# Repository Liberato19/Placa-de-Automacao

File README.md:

# Controle de Disjuntores com ESP32, Tasmota e Home Assistant

## Descrição do Projeto
Este projeto apresenta o desenvolvimento de uma placa de automação projetada para controlar **disjuntores** através de um **ESP32** com o firmware **Tasmota** instalado. O ESP32 atua como endpoint MQTT, e todas as informações e controles são exibidos no **Home Assistant**.

## Visão Geral do Projeto

### Imagem da Placa

A placa foi projetada para facilitar o controle remoto dos disjuntores, garantindo um sistema robusto e integrado.

---

## Instalação do Firmware Tasmota no ESP32

Para utilizar a placa, é necessário instalar o firmware **Tasmota** no ESP32. Certifique-se de configurar corretamente o MQTT com o seu próprio broker e seguir a pinagem descrita abaixo:

### Interface Inicial do Tasmota

### Configuração de Pinagem no Tasmota

---

## Configuração do Home Assistant

### 1. Configurar o Broker MQTT
No **Home Assistant**, configure seu Broker MQTT para a comunicação com o dispositivo Tasmota.

Assim que o MQTT estiver configurado corretamente, o dispositivo deve ser detectado automaticamente.

### Integração com o MQTT no Home Assistant

### Integração com o Tasmota

---

## Configuração da Dashboard no Home Assistant

Com a integração concluída, os botões de controle dos disjuntores podem ser adicionados à **dashboard** do Home Assistant. Isso permite o controle direto dos disjuntores com apenas um clique.

### Planta Integrada

### Botões de Controle

---

## Requisitos
- **ESP32**
- **Placa de automação**
- **Firmware Tasmota**
- **Broker MQTT** (local ou em nuvem)
- **Home Assistant** configurado

---

## Tags de Tecnologias Utilizadas

---

## Guia de Uso
1. Instale o firmware **Tasmota** no ESP32 e configure o MQTT.
2. Conecte o ESP32 à placa de automação.
3. Configure o Broker MQTT no Home Assistant.
4. Integre o dispositivo Tasmota no Home Assistant.
5. Adicione os botões à dashboard e comece a controlar os disjuntores!

---

## Imagens do Projeto

1. **PCB da Placa** 
2. **Interface Inicial do Tasmota** 
3. **Configuração de Pinagem** 
4. **Integração MQTT no Home Assistant** 
5. **Integração com o Tasmota** 

---

## Licença
Este projeto está licenciado sob a **MIT License**.

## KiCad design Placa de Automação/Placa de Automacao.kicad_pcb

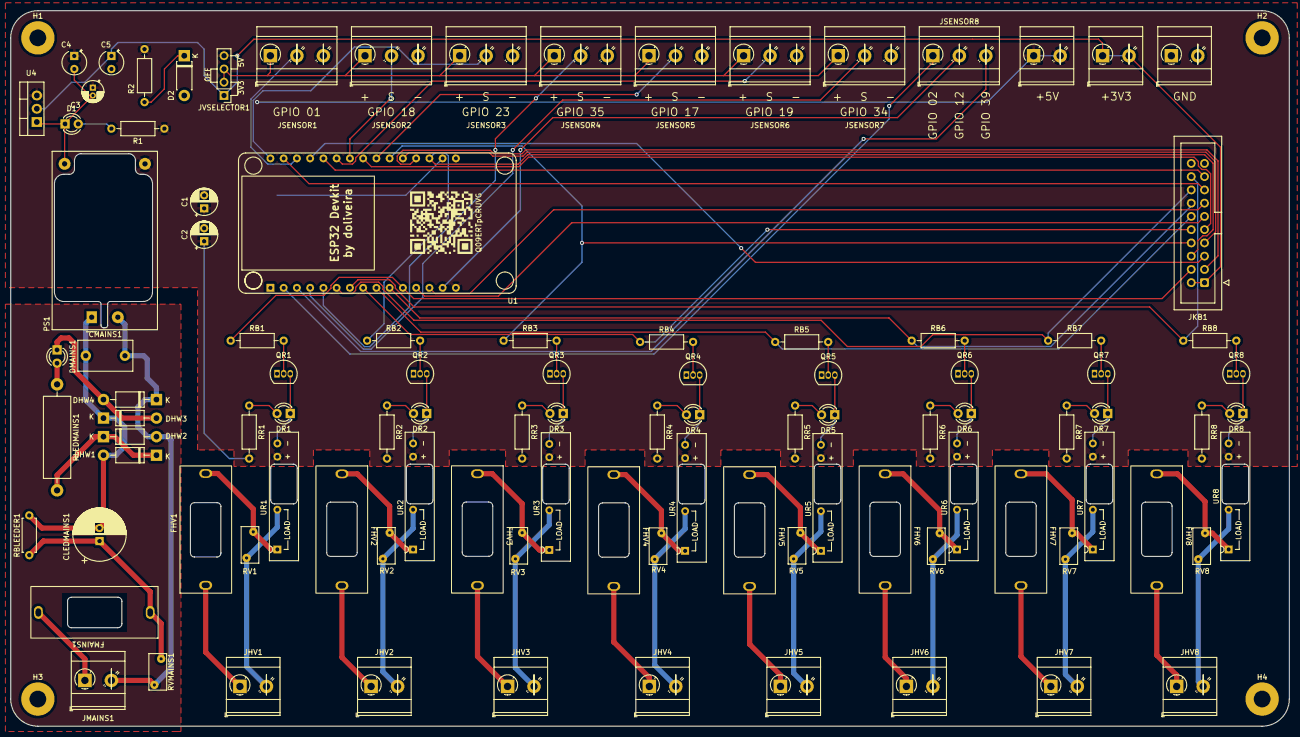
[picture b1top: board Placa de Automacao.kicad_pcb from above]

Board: 2 copper layers, 245.1 x 137.1 mm, 106 parts (0 on the bottom side), 87 nets.

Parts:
C1, C2: 10 uF; CP_Radial_D5.0mm_P2.50mm
C3: 220 uF; CP_Radial_D4.0mm_P1.50mm
C4, C5: 10 uF; CP_Radial_Tantal_D4.5mm_P2.50mm
CLEDMAINS1: 33uF; CP_Radial_D10.0mm_P2.50mm
CMAINS1: 0.1uF; C_Rect_L10.3mm_W5.7mm_P7.50mm_MKS4
D1: LED; LED_D3.0mm
D2: 5V1; D_DO-41_SOD81_P7.62mm_Horizontal
DHW1, DHW2, DHW3, DHW4: 1N4007; D_DO-41_SOD81_P10.16mm_Horizontal
DMAINS1: LED; LED_D3.0mm
DR1, DR2, DR3, DR4, DR5, DR6, DR7, DR8: LED; LED_D3.0mm
FHV1, FHV2, FHV3, FHV4, FHV5, FHV6, FHV7, FHV8: 1A; Fuseholder_Cylinder-5x20mm_Generic_Horizontal_Closed
FMAINS1: 0.5A; Fuseholder_Cylinder-5x20mm_Generic_Horizontal_Closed
G6: LOGO
H1, H2, H3, H4: MountingHole; MountingHole_3.2mm_M3_Pad
JHV1, JHV2, JHV3, JHV4, JHV5, JHV6, JHV7, JHV8: Screw_Terminal_01x02; TerminalBlock_MetzConnect_Type073_RT02602HBLU_1x02_P5.08mm_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
JKB1: Conn_02x10_Top_Bottom; IDC-Header_2x10_P2.54mm_Vertical
JMAINS1: Screw_Terminal_01x02; TerminalBlock_MetzConnect_Type073_RT02602HBLU_1x02_P5.08mm_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
JSENSOR1, JSENSOR2, JSENSOR3, JSENSOR4, JSENSOR5, JSENSOR6, JSENSOR7, JSENSOR8: Screw_Terminal_01x03; TerminalBlock_MetzConnect_Type073_RT02603HBLU_1x03_P5.08mm_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
JVSELECTOR1: Conn_01x04_Pin; PinHeader_1x04_P2.54mm_Vertical
J_GND1: Screw_Terminal_01x02; TerminalBlock_MetzConnect_Type073_RT02602HBLU_1x02_P5.08mm_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
J_POS_3V1, J_POS_5V1: Screw_Terminal_01x02; TerminalBlock_MetzConnect_Type073_RT02602HBLU_1x02_P5.08mm_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
PS1: HLK-PM01; Converter_ACDC_HiLink_HLK-PMxx
QR1, QR2, QR3, QR4, QR5, QR6, QR7, QR8: PN2222A; TO-92_Inline
R1: 160; R_Axial_DIN0207_L6.3mm_D2.5mm_P10.16mm_Horizontal
R2: 10; R_Axial_DIN0207_L6.3mm_D2.5mm_P10.16mm_Horizontal
RB1, RB2, RB3, RB4, RB5, RB6, RB7, RB8: 56; R_Axial_DIN0207_L6.3mm_D2.5mm_P10.16mm_Horizontal
RBLEEDER1: 1M; R_Axial_DIN0207_L6.3mm_D2.5mm_P7.62mm_Horizontal
RLEDMAINS1: 56k; R_Axial_DIN0516_L15.5mm_D5.0mm_P20.32mm_Horizontal
RR1, RR2, RR3, RR4, RR5, RR6, RR7, RR8: 150; R_Axial_DIN0207_L6.3mm_D2.5mm_P10.16mm_Horizontal
RV1, RV2, RV3, RV4, RV5, RV6, RV7, RV8: 250 VAC; RV_Disc_D7mm_W3.4mm_P5mm
RVMAINS1: 250 VAC; RV_Disc_D7mm_W3.4mm_P5mm
U1: ESP32_Devkit_Generic_Alt; ESP32_Devkit
U4: LM1117-3.3; TO-220-3_Vertical
UR1, UR2, UR3, UR4, UR5, UR6, UR7, UR8: G3MB-202P; PTH_W24.5_D5.5_SSR_OMRON_G3MB-202P

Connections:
+3V3: C5.1, JKB1.1, JKB1.2, JVSELECTOR1.1, J_POS_3V1.1, J_POS_3V1.2, U4.2 (VO)
+5V: C1.1, C2.1, C3.1, C4.1, JVSELECTOR1.4, J_POS_5V1.1, J_POS_5V1.2, PS1.4 (+Vout), R1.1, R2.1, RR1.2, RR2.2, RR3.2, RR4.2, RR5.2, RR6.2, RR7.2, RR8.2, U1.15 (VIN), U4.3 (VI), UR1.3, UR2.3, UR3.3, UR4.3, UR5.3, UR6.3, UR7.3, UR8.3
/volt_selector: JSENSOR1.1, JSENSOR2.1, JSENSOR3.1, JSENSOR4.1, JSENSOR5.1, JSENSOR6.1, JSENSOR7.1, JVSELECTOR1.2, JVSELECTOR1.3
GND: C1.2, C2.2, C3.2, C4.2, C5.2, D1.1 (K), D2.2 (A), JKB1.19, JKB1.20, JSENSOR1.3, JSENSOR2.3, JSENSOR3.3, JSENSOR4.3, JSENSOR5.3, JSENSOR6.3, JSENSOR7.3, J_GND1.1, J_GND1.2, PS1.3 (-Vout), QR1.1 (E), QR2.1 (E), QR3.1 (E), QR4.1 (E), QR5.1 (E), QR6.1 (E), QR7.1 (E), QR8.1 (E), U1.17 (GND), U4.1 (GND)
unnamed: CLEDMAINS1.1, FMAINS1.2, RBLEEDER1.1, RVMAINS1.1
unnamed: D1.2 (A), R1.2
unnamed: D2.1 (K), R2.2
unnamed: CLEDMAINS1.2, CMAINS1.1, DHW1.2 (A), DHW3.1 (K), PS1.1 (AC/L), RBLEEDER1.2
unnamed: DHW1.1 (K), DHW2.1 (K), RLEDMAINS1.2
unnamed: CMAINS1.2, DHW2.2 (A), DHW4.1 (K), JMAINS1.2, PS1.2 (AC/N), RVMAINS1.2
unnamed: DHW3.2 (A), DHW4.2 (A), DMAINS1.1 (K)
unnamed: DMAINS1.2 (A), RLEDMAINS1.1
unnamed: DR1.2 (A), RR1.1
unnamed: DR1.1 (K), QR1.3 (C), UR1.4
unnamed: DR2.2 (A), RR2.1
unnamed: DR2.1 (K), QR2.3 (C), UR2.4
unnamed: DR3.2 (A), RR3.1
unnamed: DR3.1 (K), QR3.3 (C), UR3.4
unnamed: DR4.2 (A), RR4.1
unnamed: DR4.1 (K), QR4.3 (C), UR4.4
unnamed: DR5.2 (A), RR5.1
unnamed: DR5.1 (K), QR5.3 (C), UR5.4
unnamed: DR6.2 (A), RR6.1
unnamed: DR6.1 (K), QR6.3 (C), UR6.4
unnamed: DR7.2 (A), RR7.1
unnamed: DR7.1 (K), QR7.3 (C), UR7.4
unnamed: DR8.2 (A), RR8.1
unnamed: DR8.1 (K), QR8.3 (C), UR8.4
unnamed: FHV1.1, RV1.2, UR1.1
unnamed: FHV2.2, RV2.2, UR2.1
unnamed: FHV3.2, RV3.2, UR3.1
unnamed: FHV4.2, RV4.2, UR4.1
unnamed: FHV5.2, RV5.2, UR5.1
unnamed: FHV6.2, RV6.2, UR6.1
unnamed: FHV7.2, RV7.2, UR7.1
unnamed: FHV8.2, RV8.2, UR8.1
unnamed: FHV1.2, JHV1.1
unnamed: JHV1.2, RV1.1, UR1.2
unnamed: FHV2.1, JHV2.1
unnamed: JHV2.2, RV2.1, UR2.2
unnamed: FHV3.1, JHV3.1
unnamed: JHV3.2, RV3.1, UR3.2
unnamed: FHV4.1, JHV4.1
unnamed: JHV4.2, RV4.1, UR4.2
unnamed: FHV5.1, JHV5.1
unnamed: JHV5.2, RV5.1, UR5.2
unnamed: FHV6.1, JHV6.1
unnamed: JHV6.2, RV6.1, UR6.2
unnamed: FHV7.1, JHV7.1
unnamed: JHV7.2, RV7.1, UR7.2
unnamed: FHV8.1, JHV8.1
unnamed: JHV8.2, RV8.1, UR8.2
unnamed: FMAINS1.1, JMAINS1.1
unnamed: QR1.2 (B), RB1.2
unnamed: QR2.2 (B), RB2.2
unnamed: QR3.2 (B), RB3.2
unnamed: QR4.2 (B), RB4.2
unnamed: QR5.2 (B), RB5.2
unnamed: QR6.2 (B), RB6.2
unnamed: QR7.2 (B), RB7.2
unnamed: QR8.2 (B), RB8.2
bidirectional_pin01: JSENSOR1.2, U1.28 (GPIO1/UART0_TXD)
bidirectional_pin02: JSENSOR5.2, U1.22 (GPIO17/UART2_TXD)
bidirectional_pin03: JSENSOR2.2, U1.24 (GPIO18/VSPI_CLK)
bidirectional_pin04: JSENSOR6.2, U1.25 (GPIO19/VSPI_MISO)
bidirectional_pin05: JSENSOR3.2, U1.30 (GPIO23/VSPI_MOSI)
bidirectional_pin06: JSENSOR7.2, U1.4 (GPIO34/ADC1_6/RTC_IO4)
bidirectional_pin07: JSENSOR4.2, U1.5 (GPIO35/ADC1_7/RTC_IO5)
bidirectional_pin08: JSENSOR8.2, U1.14 (GND)
bidirectional_pin09: JSENSOR8.1, U1.2 (GPIO36/ADC1_0/RTC_IO0/SENSORVP)
bidirectional_pin10: JSENSOR8.3, U1.3 (GPIO39/ADC1_3/RTC_IO3/SENSORVN)
button_Relay01: JKB1.3, U1.19 (GPIO2/ADC2_2/RTC_IO12/TOUCH2)
button_Relay02: JKB1.5, U1.27 (GPIO3/UART0_RXD)
button_Relay03: JKB1.7, U1.20 (GPIO4/ADC2_0/RTC_IO10/TOUCH0)
button_Relay04: JKB1.9, U1.23 (GPIO5/VSPI_CS0)
button_Relay05: JKB1.11, U1.12 (GPIO12/ADC2_5/RTC_IO15/TOUCH5/HSPI_MISO)
button_Relay06: JKB1.13, U1.13 (GPIO13/ADC2_4/RTC_IO14/TOUCH4/HSPI_MOSI)
button_Relay07: JKB1.15, U1.29 (GPIO22/SCL)
button_Relay08: JKB1.17, U1.26 (GPIO21/SDA)
rele_01: JKB1.4, RB1.1, U1.11 (GPIO14/ADC2_6/RTC_IO16/TOUCH6/HSPI_CLK)
rele_02: JKB1.6, RB2.1, U1.18 (GPIO15/ADC2_3/RTC_IO13/TOUCH3/HSPI_CS0)
rele_03: JKB1.8, RB3.1, U1.21 (GPIO16/UART2_RXD)
rele_04: JKB1.10, RB4.1, U1.8 (GPIO25/ADC2_8/RTC_IO6/DAC_1)
rele_05: JKB1.12, RB5.1, U1.9 (GPIO26/ADC2_9/RTC_IO7/DAC_2)
rele_06: JKB1.14, RB6.1, U1.10 (GPIO27/ADC2_7/RTC_IO17/TOUCH7)
rele_07: JKB1.16, RB7.1, U1.6 (GPIO32/ADC1_4/RTC_IO9/TOUCH9)
rele_08: JKB1.18, RB8.1, U1.7 (GPIO33/ADC1_5/RTC_IO8/TOUCH8)

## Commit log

2024-12-17 Rename image.png to Placa de Automacao.png
2024-12-17 Rename Captura de tela 2024-12-17 123523.png to PCB
2024-12-17 Rename PCB to PCB.png
